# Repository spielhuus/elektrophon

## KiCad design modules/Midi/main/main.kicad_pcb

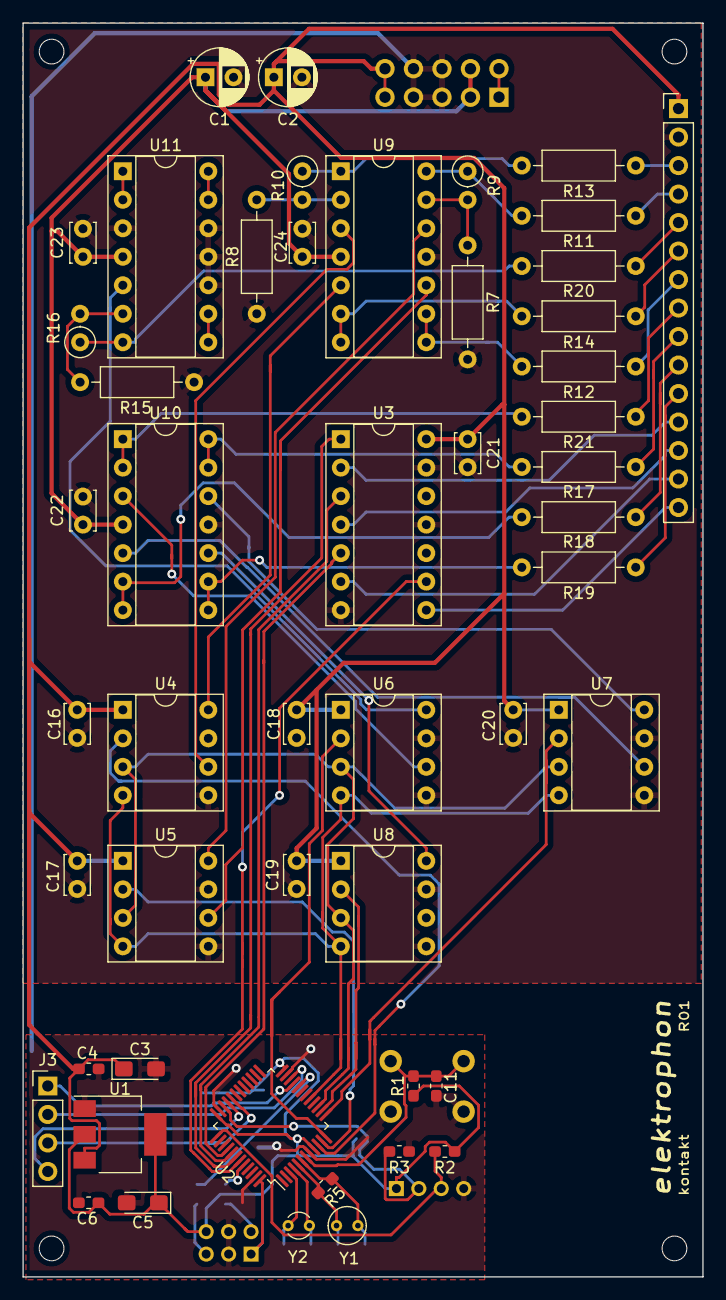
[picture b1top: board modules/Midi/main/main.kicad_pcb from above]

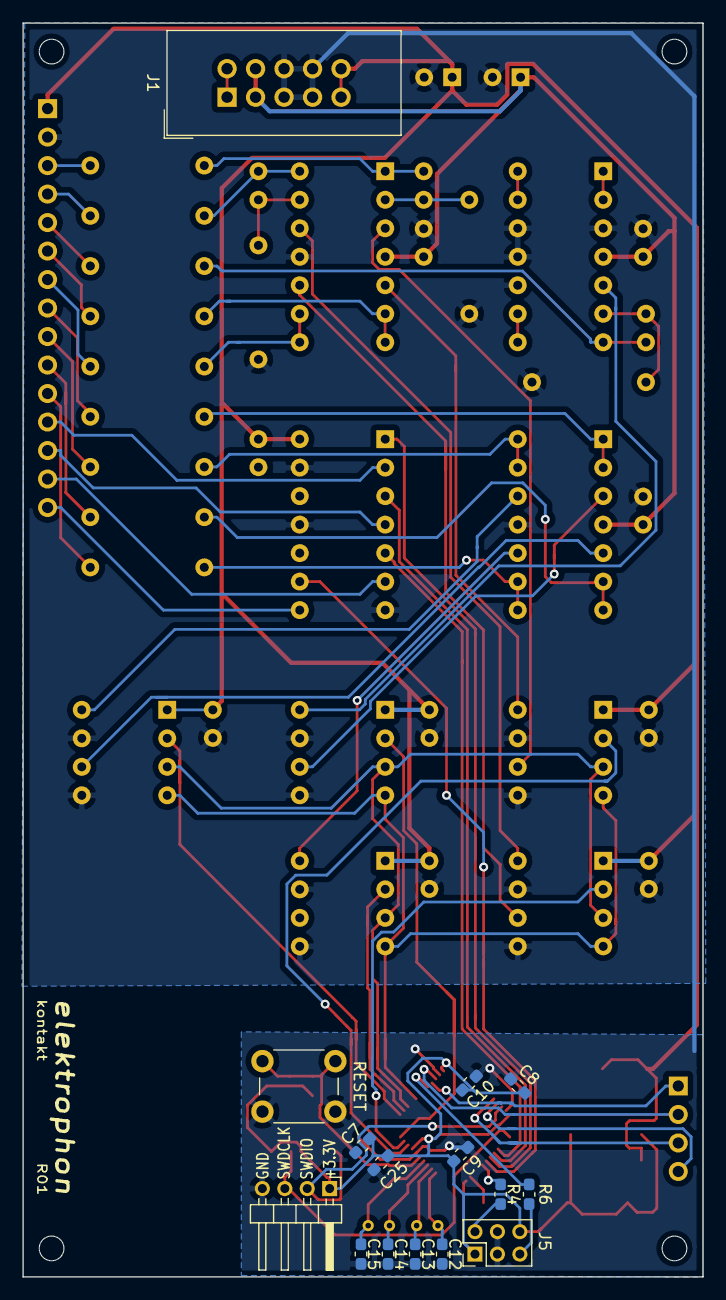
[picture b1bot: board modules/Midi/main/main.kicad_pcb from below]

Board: 2 copper layers, 60.6 x 111.8 mm, 69 parts (15 on the bottom side), 68 nets.

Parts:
C1, C2: 10u; CP_Radial_D5.0mm_P2.50mm
C3: 100u; CP_EIA-3216-18_Kemet-A_Pad1.58x1.35mm_HandSolder
C4, C6, C8, C9, C10, C11: 100n; C_0603_1608Metric_Pad1.05x0.95mm_HandSolder
C5: 330u; CP_EIA-3216-10_Kemet-I_Pad1.58x1.35mm_HandSolder
C7: 10n; C_0603_1608Metric_Pad1.05x0.95mm_HandSolder
C12, C13, C14, C15: 20p; C_0603_1608Metric_Pad1.05x0.95mm_HandSolder
C16, C17, C18, C19, C20, C21, C22, C23, C24: 0.1u; C_Disc_D3.4mm_W2.1mm_P2.50mm
C25: 1u; C_0603_1608Metric_Pad1.05x0.95mm_HandSolder
H1, H2, H3, H4: MountingHole; MountingHole_2.2mm_M2
J1: IDC Header; IDC-Header_2x05_P2.54mm_Vertical
J2: Conn_01x15_Female; PinHeader_1x15_P2.54mm_Vertical
J3: Conn_01x04_Male; PinHeader_1x04_P2.54mm_Vertical
J4: SWD; PinHeader_1x04_P2.00mm_Horizontal
J5: Conn_02x03_Counter_Clockwise; PinHeader_2x03_P2.00mm_Vertical
R1, R2, R3: 10k; R_0603_1608Metric_Pad1.05x0.95mm_HandSolder
R4, R6: 100k; R_0603_1608Metric_Pad1.05x0.95mm_HandSolder
R5: 1M; R_0603_1608Metric_Pad1.05x0.95mm_HandSolder
R7, R8, R15: 22k; R_Axial_DIN0207_L6.3mm_D2.5mm_P10.16mm_Horizontal
R9, R10, R16: 17k; R_Axial_DIN0207_L6.3mm_D2.5mm_P2.54mm_Vertical
R11, R12, R13, R14, R17, R18, R19, R20, R21: 1k; R_Axial_DIN0207_L6.3mm_D2.5mm_P10.16mm_Horizontal
RESET: SW_Push; SW_PUSH_6mm
U1: AMS1117-3.3; SOT-223-3_TabPin2
U2: STM32F103C8Tx; LQFP-48_7x7mm_P0.5mm
U3: 40106; DIP-14_W7.62mm_Socket
U4, U5, U6, U7, U8: MCP4822; DIP-8_W7.62mm_Socket
U9, U10, U11: LM324; DIP-14_W7.62mm_Socket
Y1: 8MHz; Crystal_Round_D3.0mm_Vertical
Y2: 32.768K; Crystal_Round_D2.0mm_Vertical

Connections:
+3V3: C5.1, C6.2, C7.2, C8.2, C9.2, C10.2, C25.2, J4.1, J5.1, J5.6, R1.2, R2.1, U1.2, U2.9, U2.24, U2.36, U2.48
+5V: C2.1, C3.1, C4.2, C16.1, C17.1, C18.1, C19.1, C20.1, C21.1, J1.9, J1.10, J2.1, U1.3, U3.14, U4.1, U5.1, U6.1, U7.1, U8.1
+15V: C1.1, C22.1, C23.1, C24.1, J1.3, J1.4, U9.4, U10.4, U11.4
-15V: J1.1, J1.2
/Analog Circuit/SIG_NOTE_1: U4.6, U9.3
/Analog Circuit/SIG_NOTE_2: U5.8, U9.12
/Analog Circuit/SIG_NOTE_3: U6.8, U11.5
/Analog Circuit/SIG_PITCH_BEND_1: U7.8, U10.12
/Analog Circuit/SIG_PITCH_BEND_2: U7.6, U10.5
/Analog Circuit/SIG_PITCH_BEND_3: U8.8, U10.10
/Analog Circuit/SIG_VELOCITY_1: U4.8, U9.5
/Analog Circuit/SIG_VELOCITY_2: U5.6, U9.10
/Analog Circuit/SIG_VELOCITY_3: U6.6, U10.3
/STM32 Board/BOOT0: R4.1, U2.44
/STM32 Board/BOOT1: R6.1, U2.20
/STM32 Board/OSCIN: C14.1, R5.1, U2.5, Y1.1
/STM32 Board/OSCOUT: C15.1, R5.2, U2.6, Y1.2
/STM32 Board/PC14: C12.1, U2.3, Y2.1
/STM32 Board/PC15: C13.1, U2.4, Y2.2
/STM32 Board/RESET: C11.2, R1.1, RESET.2, U2.7
/STM32 Board/SWDCLK: J4.3, R2.2, U2.37
/STM32 Board/SWDIO: J4.2, R3.2, U2.34
CS_1: U2.10, U4.2
CS_2: U2.11, U5.2
CS_3: U2.12, U6.2
CS_4: U2.13, U7.2
CS_5: U2.14, U8.2
GND: C1.2, C2.2, C3.2, C4.1, C5.2, C6.1, C7.1, C8.1, C9.1, C10.1, C11.1, C12.2, C13.2, C14.2, C15.2, C16.2, C17.2, C18.2, C19.2, C20.2, C21.2, C22.2, C23.2, C24.2, C25.1, J1.5, J1.6, J1.7, J1.8, J2.2, J4.4, J5.3, J5.4, R3.1, R7.1, R8.1, R15.1, RESET.1, U1.1, U2.8, U2.23, U2.35, U2.47, U3.7, U3.11, U3.13, U4.5, U4.7, U5.5, U5.7, U6.5, U6.7, U7.5, U7.7, U8.5, U8.7, U9.11, U10.11, U11.3, U11.10, U11.11, U11.12
LED_ACTIVITY: J3.1, U2.21
LED_CONNECT: J3.2, U2.22
MOSI: U2.17, U4.4, U5.4, U6.4, U7.4, U8.4
unnamed: J5.2, R4.2
unnamed: J5.5, R6.2
unnamed: R7.2, R9.2, U9.13
unnamed: R10.1, R13.2, U9.1
unnamed: R8.2, R10.2, U9.2
unnamed: R9.1, R11.2, U9.14
unnamed: R12.2, U9.8, U9.9
unnamed: R14.2, U9.6, U9.7
unnamed: R15.2, R16.2, U11.6
unnamed: R16.1, R20.2, U11.7
unnamed: R17.2, U10.13, U10.14
unnamed: R18.2, U10.6, U10.7
unnamed: R19.2, U10.8, U10.9
unnamed: R21.2, U10.1, U10.2
unnamed: U11.1, U11.2
unnamed: U11.8, U11.9
unnamed: U11.13, U11.14
Note_1: J2.3, R13.1
Note_2: J2.4, R11.1
Note_3: J2.5, R20.1
OUT_CLOCK: J2.15, U3.8
OUT_TRIGGER_1: J2.12, U3.2
OUT_TRIGGER_2: J2.13, U3.4
OUT_TRIGGER_3: J2.14, U3.6
PA11: J3.3, U2.32
PA12: J3.4, U2.33
PITCH_BEND_1: J2.9, R17.1
PITCH_BEND_2: J2.10, R18.1
PITCH_BEND_3: J2.11, R19.1
SCK: U2.15, U4.3, U5.3, U6.3, U7.3, U8.3
SIG_CLOCK: U2.43, U3.9
SIG_TRIGGER_1: U2.42, U3.1
SIG_TRIGGER_2: U2.41, U3.3
SIG_TRIGGER_3: U2.40, U3.5
Velocity_1: J2.6, R14.1
Velocity_2: J2.7, R12.1
Velocity_3: J2.8, R21.1

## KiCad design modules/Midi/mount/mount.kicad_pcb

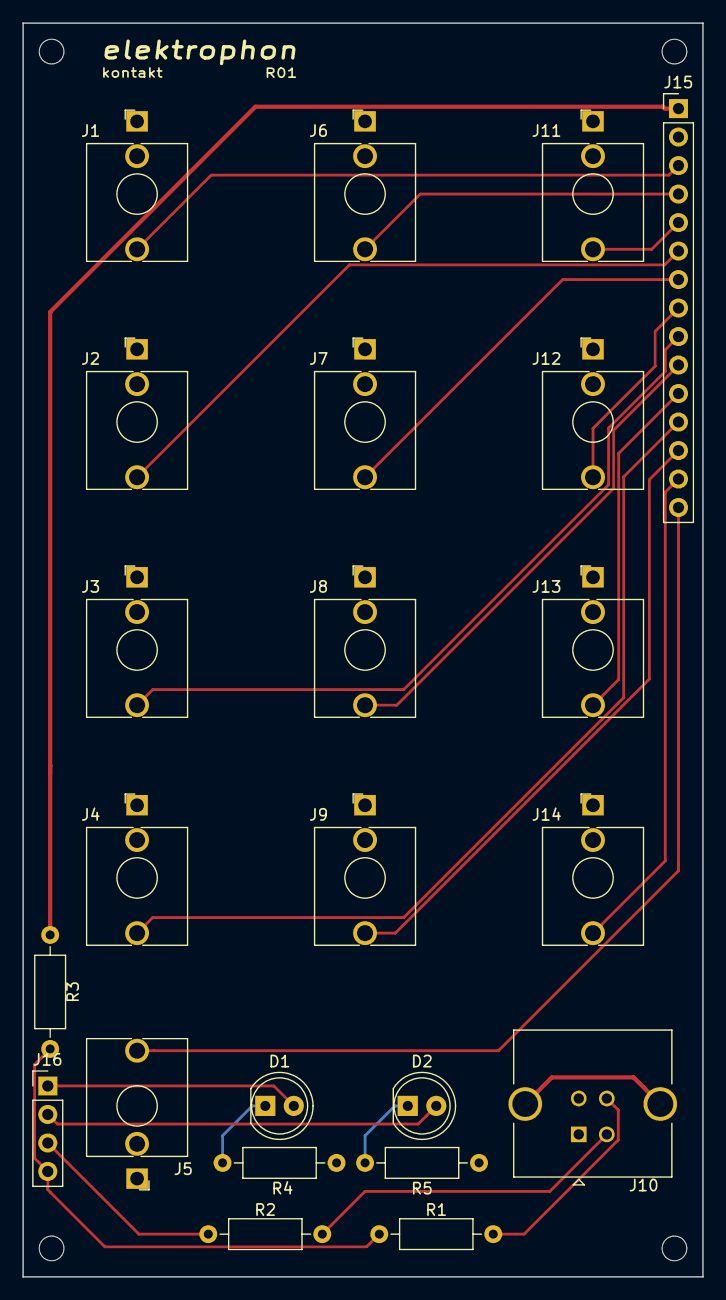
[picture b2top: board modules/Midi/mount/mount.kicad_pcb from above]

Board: 2 copper layers, 60.6 x 111.8 mm, 27 parts (0 on the bottom side), 23 nets.

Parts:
D1, D2: LED; LED_D5.0mm
H1, H2, H3, H4: MountingHole; MountingHole_2.2mm_M2
J1, J2, J3, J4, J5, J6, J7, J8, J9, J11, J12, J13, J14: INPUT; Jack_3.5mm_WQP-PJ398SM_Vertical
J10: USB_B; USB_B_TE_5787834_Vertical
J15: Conn_01x15_Male; PinHeader_1x15_P2.54mm_Vertical
J16: Conn_01x04_Male; PinHeader_1x04_P2.54mm_Vertical
R1, R2, R3: 20; R_Axial_DIN0207_L6.3mm_D2.5mm_P10.16mm_Horizontal
R4, R5: 56; R_Axial_DIN0207_L6.3mm_D2.5mm_P10.16mm_Horizontal

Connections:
+5V: J15.1, R3.2
/PA11: J16.3, R2.1
/PA12: J16.4, R1.1, R3.1
GND: J1.S, J2.S, J3.S, J4.S, J5.S, J6.S, J7.S, J8.S, J9.S, J10.4, J11.S, J12.S, J13.S, J14.S, J15.2, R4.2, R5.2
LED_ACTIVITY: D1.2, J16.1
LED_CONNECT: D2.2, J16.2
unnamed: D1.1, R4.1
unnamed: D2.1, R5.1
unnamed: J10.2, R2.2
unnamed: J10.3, R1.2
Note_1: J1.T, J15.3
Note_2: J6.T, J15.4
Note_3: J11.T, J15.5
OUT_CLOCK: J5.T, J15.15
OUT_TRIGGER_1: J4.T, J15.12
OUT_TRIGGER_2: J9.T, J15.13
OUT_TRIGGER_3: J14.T, J15.14
PITCH_BEND_1: J3.T, J15.9
PITCH_BEND_2: J8.T, J15.10
PITCH_BEND_3: J13.T, J15.11
Velocity_1: J2.T, J15.6
Velocity_2: J7.T, J15.7
Velocity_3: J12.T, J15.8

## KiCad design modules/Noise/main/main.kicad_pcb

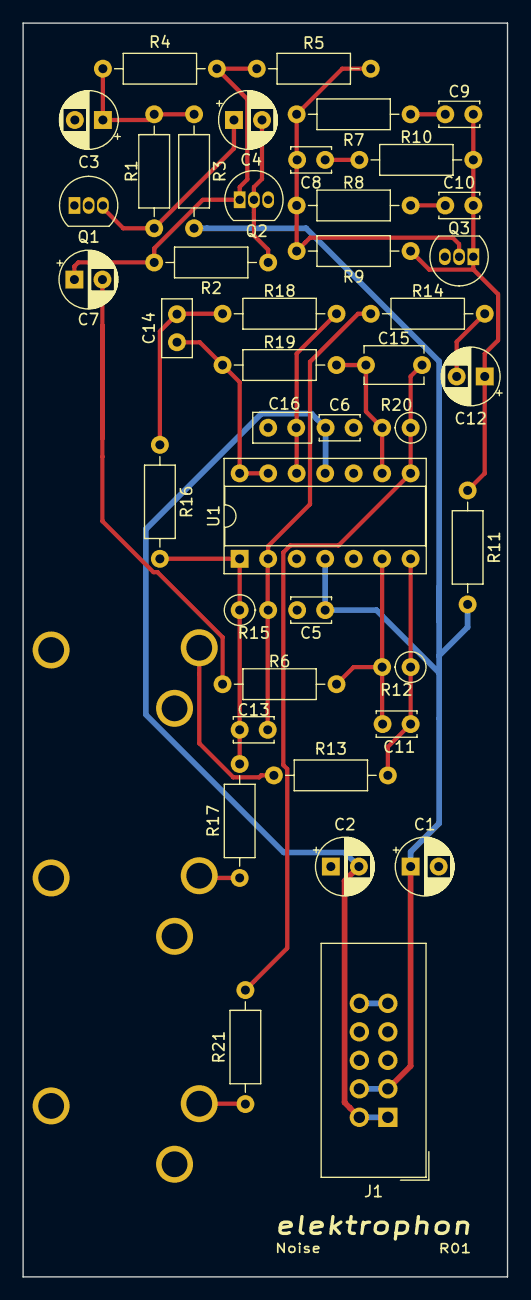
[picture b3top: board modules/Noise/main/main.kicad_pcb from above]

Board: 2 copper layers, 43.2 x 111.8 mm, 45 parts (0 on the bottom side), 27 nets.

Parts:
C1, C2, C7, C12: 10u; CP_Radial_D5.0mm_P2.50mm
C3, C4: 47u; CP_Radial_D5.0mm_P2.50mm
C5, C6: 0.1u; C_Disc_D3.4mm_W2.1mm_P2.50mm
C8: 3n3; C_Disc_D3.4mm_W2.1mm_P2.50mm
C9: 1n; C_Disc_D3.4mm_W2.1mm_P2.50mm
C10: 47n; C_Disc_D3.4mm_W2.1mm_P2.50mm
C11, C13: 10p; C_Disc_D3.4mm_W2.1mm_P2.50mm
C14, C16: 1u; C_Disc_D5.0mm_W2.5mm_P2.50mm
C15: 150n; C_Disc_D5.1mm_W3.2mm_P5.00mm
J1: IDC Header; IDC-Header_2x05_P2.54mm_Vertical
Q1, Q2, Q3: BC547; TO-92_Inline
R1: 47k; R_Axial_DIN0207_L6.3mm_D2.5mm_P10.16mm_Horizontal
R2: 150k; R_Axial_DIN0207_L6.3mm_D2.5mm_P10.16mm_Horizontal
R3: 22; R_Axial_DIN0207_L6.3mm_D2.5mm_P10.16mm_Horizontal
R4, R19: 10k; R_Axial_DIN0207_L6.3mm_D2.5mm_P10.16mm_Horizontal
R5: 82k; R_Axial_DIN0207_L6.3mm_D2.5mm_P10.16mm_Horizontal
R6, R16, R18: 33k; R_Axial_DIN0207_L6.3mm_D2.5mm_P10.16mm_Horizontal
R7: 18k; R_Axial_DIN0207_L6.3mm_D2.5mm_P10.16mm_Horizontal
R8: 390k; R_Axial_DIN0207_L6.3mm_D2.5mm_P10.16mm_Horizontal
R9: 1M; R_Axial_DIN0207_L6.3mm_D2.5mm_P10.16mm_Horizontal
R10: 100k; R_Axial_DIN0207_L6.3mm_D2.5mm_P10.16mm_Horizontal
R11: 3k9; R_Axial_DIN0207_L6.3mm_D2.5mm_P10.16mm_Horizontal
R12, R15: 470k; R_Axial_DIN0207_L6.3mm_D2.5mm_P2.54mm_Vertical
R13, R17, R21: 1k; R_Axial_DIN0207_L6.3mm_D2.5mm_P10.16mm_Horizontal
R14: 8k2; R_Axial_DIN0207_L6.3mm_D2.5mm_P10.16mm_Horizontal
R20: 220k; R_Axial_DIN0207_L6.3mm_D2.5mm_P2.54mm_Vertical
U1: LM324; DIP-14_W7.62mm_Socket
U2, U3, U4: PJ302M

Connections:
+5V: J1.9, J1.10
+15V: C1.1, C5.1, J1.3, J1.4, R3.1, R11.2, U1.4
-15V: C2.2, C6.2, J1.1, J1.2, U1.11
GND: C1.2, C2.1, C3.2, C5.2, C6.1, C16.1, J1.5, J1.6, J1.7, J1.8, Q1.2, Q2.3, Q3.3, U1.3, U1.5, U1.10, U2.GND, U3.GND, U4.GND
unnamed: C3.1, R1.1, R3.2, R4.1
unnamed: C4.1, Q1.3, R1.2
unnamed: C4.2, Q2.2, R2.2
unnamed: C7.1, Q2.1, R2.1, R4.2, R5.2
unnamed: C7.2, R6.2
unnamed: C8.1, R10.2
unnamed: C8.2, Q3.2, R5.1, R7.2, R8.2, R9.2
unnamed: C9.2, R7.1
unnamed: C9.1, C10.1, C12.1, Q3.1, R9.1, R10.1, R11.1
unnamed: C10.2, R8.1
unnamed: C11.1, R12.1, R13.2, U1.7
unnamed: C11.2, R6.1, R12.2, U1.6
unnamed: C12.2, R14.2
unnamed: C13.1, R15.1, R16.2, R17.2, U1.1
unnamed: C13.2, R14.1, R15.2, U1.2
unnamed: C14.1, R19.2, U1.13, U1.14
unnamed: C14.2, R16.1, R18.2
unnamed: C15.1, R20.1, R21.2, U1.8
unnamed: C15.2, R19.1, R20.2, U1.9
unnamed: C16.2, R18.1, U1.12
unnamed: R13.1, U2.TIP
unnamed: R17.1, U3.TIP
unnamed: R21.1, U4.TIP

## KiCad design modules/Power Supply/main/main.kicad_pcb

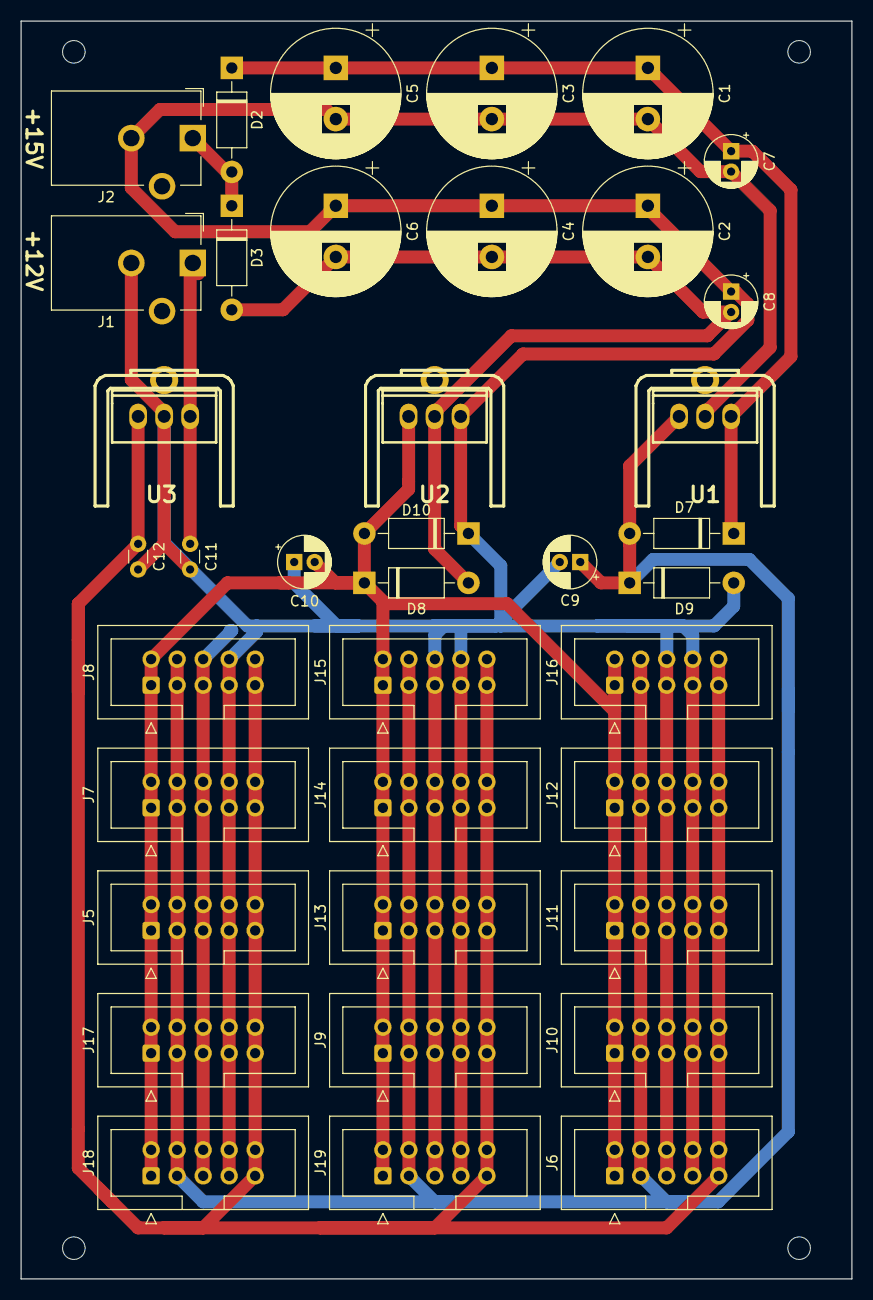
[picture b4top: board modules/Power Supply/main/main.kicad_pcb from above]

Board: 2 copper layers, 81.1 x 122.8 mm, 42 parts (0 on the bottom side), 8 nets.

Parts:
C1, C2, C3, C4, C5, C6: 3300uF; CP_Radial_D12.5mm_P5.00mm
C7, C8, C9, C10: 1uF; CP_Radial_D5.0mm_P2.00mm
C11: 0.33; C_Disc_D3.0mm_W1.6mm_P2.50mm
C12: 0.1; C_Disc_D3.0mm_W1.6mm_P2.50mm
D2, D3, D7, D8, D9, D10: 1N4004; D_DO-41_SOD81_P10.16mm_Horizontal
H1, H2, H3, H4: MountingHole; MountingHole_2.2mm_M2
J1, J2: Barrel_Jack_Switch; BarrelJack_CUI_PJ-102AH_Horizontal
J5, J6, J7, J8, J9, J10, J11, J12, J13, J14, J15, J16, J17, J18, J19: IDC_Header; IDC-Header_2x05_P2.54mm_Vertical
U1: L7815; to220_std_5772
U2: L7915; to220_std_5772
U3: L7805; to220_std_5772

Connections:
15V_AC: D2.2, D3.1, J2.1
15V_N: C1.2, C2.1, C3.2, C4.1, C5.2, C6.1, C7.2, C8.1, C9.2, C10.1, C11.2, C12.2, D9.2, D10.1, J1.2, J2.2, J5.5, J5.6, J5.7, J5.8, J6.5, J6.6, J6.7, J6.8, J7.5, J7.6, J7.7, J7.8, J8.5, J8.6, J8.7, J8.8, J9.5, J9.6, J9.7, J9.8, J10.5, J10.6, J10.7, J10.8, J11.5, J11.6, J11.7, J11.8, J12.5, J12.6, J12.7, J12.8, J13.5, J13.6, J13.7, J13.8, J14.5, J14.6, J14.7, J14.8, J15.5, J15.6, J15.7, J15.8, J16.5, J16.6, J16.7, J16.8, J17.5, J17.6, J17.7, J17.8, J18.5, J18.6, J18.7, J18.8, J19.5, J19.6, J19.7, J19.8, U1.2, U2.1, U3.2
+5V: C12.1, J5.9, J5.10, J6.9, J6.10, J7.9, J7.10, J8.9, J8.10, J9.9, J9.10, J10.9, J10.10, J11.9, J11.10, J12.9, J12.10, J13.9, J13.10, J14.9, J14.10, J15.9, J15.10, J16.9, J16.10, J17.9, J17.10, J18.9, J18.10, J19.9, J19.10, U3.3
+12V: C11.1, J1.1, U3.1
+15V: C9.1, D7.2, D9.1, J5.3, J5.4, J6.3, J6.4, J7.3, J7.4, J8.3, J8.4, J9.3, J9.4, J10.3, J10.4, J11.3, J11.4, J12.3, J12.4, J13.3, J13.4, J14.3, J14.4, J15.3, J15.4, J16.3, J16.4, J17.3, J17.4, J18.3, J18.4, J19.3, J19.4, U1.3
-15V: C10.2, D8.1, D10.2, J5.1, J5.2, J6.1, J6.2, J7.1, J7.2, J8.1, J8.2, J9.1, J9.2, J10.1, J10.2, J11.1, J11.2, J12.1, J12.2, J13.1, J13.2, J14.1, J14.2, J15.1, J15.2, J16.1, J16.2, J17.1, J17.2, J18.1, J18.2, J19.1, J19.2, U2.3
unnamed: C1.1, C3.1, C5.1, C7.1, D2.1, D7.1, U1.1
unnamed: C2.2, C4.2, C6.2, C8.2, D3.2, D8.2, U2.2

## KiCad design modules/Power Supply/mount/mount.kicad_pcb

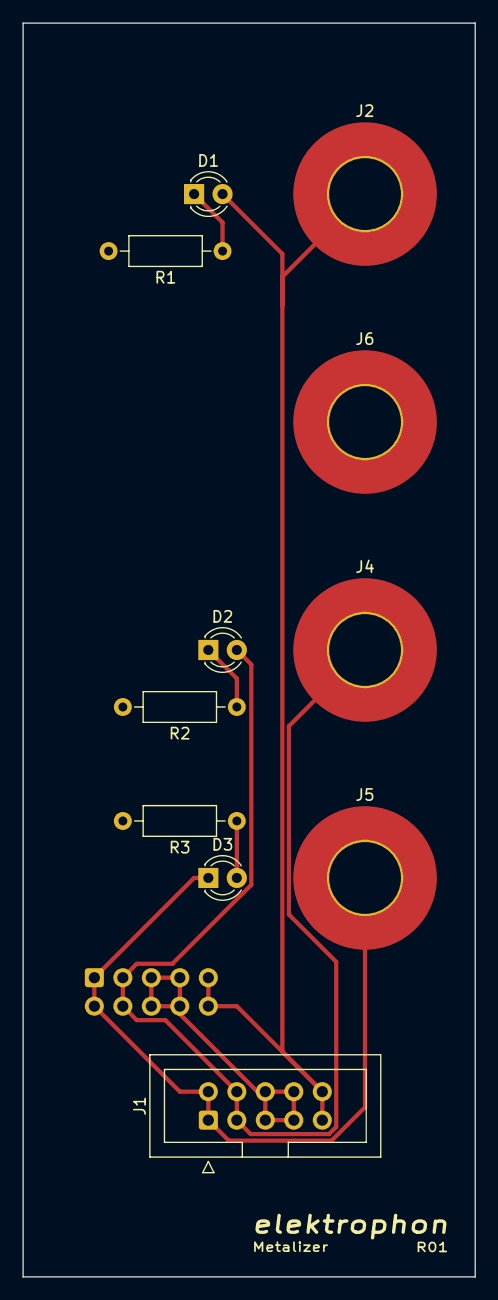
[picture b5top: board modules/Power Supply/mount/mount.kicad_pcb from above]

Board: 2 copper layers, 40.3 x 111.8 mm, 12 parts (1 on the bottom side), 7 nets.

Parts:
D1, D2, D3: LED; LED_D3.0mm
J1, J3: IDC Header; IDC-Header_2x05_P2.54mm_Vertical
J2, J4, J5, J6: Conn_01x01_Female; MountingHole_6.4mm_M6_Pad_TopBottom
R1, R2, R3: R; R_Axial_DIN0207_L6.3mm_D2.5mm_P10.16mm_Horizontal

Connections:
+5V: D1.2, J1.9, J1.10, J2.1, J3.9, J3.10
+15V: D2.2, J1.3, J1.4, J3.3, J3.4, J4.1
-15V: D3.1, J1.1, J1.2, J3.1, J3.2, J5.1
GND: J1.5, J1.6, J1.7, J1.8, J3.5, J3.6, J3.7, J3.8, J6.1, R1.2, R2.2, R3.2
unnamed: D1.1, R1.1
unnamed: D2.1, R2.1
unnamed: D3.2, R3.1

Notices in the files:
modules/Noise/main/main.kicad_pcb:
License CC BY 4.0 - Attribution 4.0 International
